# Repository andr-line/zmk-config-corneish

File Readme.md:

# Matrix keyboard
This is my attempt at making a keyboard that is as compact as possible but still useable, meaning that all the letter keys are still where they should be (just ortholinear). The pcb design is in hardware as a kicad file or as the finished gerber files I needed for pcbway.

## Important
This is my first keyboard, it‘s not perfect. The pcb does not include an off switch or reset button since I didn‘t find them important, as I will be using the keyboard quasy always and it did not really degrade the battery life too much for me. If you try to build this keyboard, **add a reset button** since pairing is extremely difficult without one.

The files are adapted to me, the bottom keys for example are shifted by one since I always typed like that. Also one of my controllers was faulty so I had to add an additional pin that is not needed normaly (pin 101).

## Unimportant
Recently I found the [36 key keyboard by dilshod](https://github.com/dilshod/36-choc-key-ortholinear-split) which is basically the same keyboard but with better execution. I am also planning on making a new version / revision that uses the kailh PG1316S switches (that are not yet commonly available as far as I know) as seen in [mikeholschers mikefive](https://github.com/mikeholscher/zmk-config-mikefive) keyboard as they could potentially reduce the thickness greatly.

[Keymap editor by nickcoutsos](https://nickcoutsos.github.io/keymap-editor/)

## Building instructions
You will need 36 choc v1 (Kailh 1350) switches, two nice!nano controllers, two batteries as recommended on the [nice!keyboards](https://nicekeyboards.com) site (I used the 301230 battery found on aliexpress as it fits nicely underneath the nice!nanos) and the machine pins to mount the nice!nano controllers to the board.

On the side where the silk screen (labels of the controllers pins) on the board are on top (will be covered by the battery) you have to solder the solder bridges as indicated by their frames. On the other board (where the silk screen is on the bottom) you have to solder them in the other way (solder the middle pad to the one that is not in the same frame). Then you have to solder the nice!nanos and batteries, and finally solder all the switches. Make sure that all solder connections are good.

If you haven't flashed the firmware yet, do it now and test if it works. You can connect each half via usb cable to test the hardware. If for some reason one of the pins of the nice!nano should breake (as was the case for me) you can use the 101, 102 and 107 pins in the middle of the nice!nano as backup (and change the files accordingly). To connect the two halves together you must reset them at the same time. This is very difficult without a reset button **hence you should add one** before ordering the pcbs. I managed to do it by bridging the reset pin using a pair of metal scissors on both halves simultaneously. Once this has worked you should be good to go. I recommend the above keymap editor to configure the keymap as it greatly simplifies the process.

## Final product
The keyboard looks like this, with an iPhone 11 for size comparison.

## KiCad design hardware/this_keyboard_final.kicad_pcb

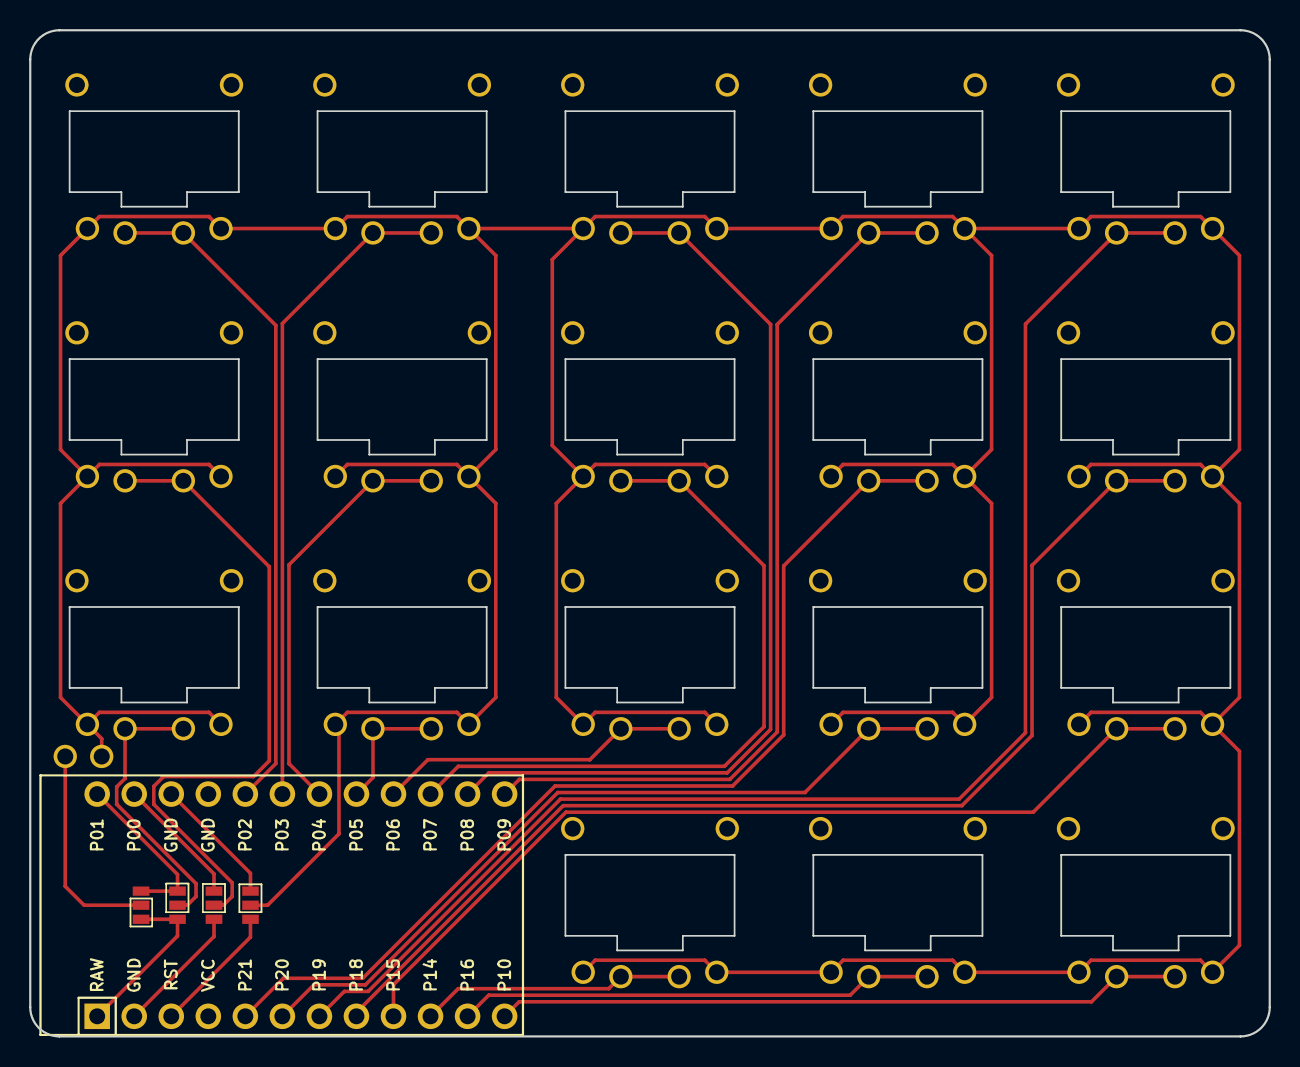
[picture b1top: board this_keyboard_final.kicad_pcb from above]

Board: 2 copper layers, 85.0 x 69.0 mm, 25 parts (0 on the bottom side), 24 nets.

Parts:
J1, J2: Kailh_PG1232
J3, J4, J5, J6: Jumper
MCU1: ProMicro
S1, S2, S3, S4, S5, S6, S7, S8, S9, S10, S11, S12, S13, S14, S15, S16, S17, S18: Kailh_PG1232

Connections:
GND: J1.1, J5.3, J6.1, MCU1.2, MCU1.15, MCU1.16, S1.1, S2.1, S3.1, S4.1, S5.1, S6.1, S7.1, S8.1, S9.1, S10.1, S11.1, S12.1, S13.1, S14.1, S15.1, S16.1, S17.1, S18.1
P0: J5.1, MCU1.14
P0_1: J5.1, S2.2
P1: J3.3, J4.1, MCU1.13
P1_1: J4.1, S1.2
P2: MCU1.17, S3.2
P3: MCU1.18, S6.2
P4: MCU1.19, S5.2
P5: MCU1.20, S4.2
P6: MCU1.21, S7.2
P7: MCU1.22, S8.2
P8: MCU1.23, S9.2
P9: MCU1.24, S12.2
P10: MCU1.12, S18.2
P14: MCU1.10, S16.2
P15: MCU1.9, S13.2
P16: MCU1.11, S17.2
P18: MCU1.8, S14.2
P19: MCU1.7, S15.2
P20: MCU1.6, S10.2
P21: MCU1.5, S11.2
RAW: J3.1, J4.3, MCU1.1
RAW_1: J2.1, J3.1
RST: J6.3, MCU1.3

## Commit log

2023-03-27 Initial User Config.
2023-03-27 Initial setup using zmk documentation
2023-03-27 changed things
2023-03-27 trying to get it to work
2023-03-27 Defined matrix cols manually
2023-03-27 added zmk/matrix.h
2023-03-27 Separated the two default transforms
2023-03-27 Using chosen ...=&matrix_left;
2023-03-27 Back to two different default_transforms
2023-03-28 Moved matrix_side definitions to matrix.dsi file
2023-03-28 Setup like vallacks piano
2023-03-28 Changed piano to matrix
2023-03-28 Changed offset to correct value
2023-03-28 Changed layer 0 and 1
2023-03-28 Fixed missing number after BT_SEL
2023-03-28 Fixed BSPC
2023-03-28 Added reset in top outside corners on layer 2
2023-03-28 Commented out 2nd and 3rd layer for testing
2023-03-28 Try try again
2023-03-28 Remade layer 0 and added reset
2023-03-28 Formatted and added bootloader and navigation
2023-03-28 Fixed backspace
2023-03-28 Added a reset combo for each half
2023-03-28 Added settings reset
2023-04-01 Added tab on left pinkie
2023-04-01 Changed right key definition
2023-04-03 Added layer definitions
2023-04-03 changed pin definition order
2023-04-03 Changed left key positions to match pin definition
2023-04-04 Added Pin 11 for testing
2023-04-18 Added a nice_nano pin definition for trial
2023-04-18 Removed pin 11
2023-04-19 Removed pin 11 because it wasnt working
2023-04-19 added hardware files
2023-04-19 Gitignore test
2023-04-19 Added readme
2023-04-19 Added image of keyboard
2023-04-19 Added image to readme
2023-04-20 Added gpio1 pin definition
2023-04-20 removed reset bindings
2023-04-20 Removed further reset binding
2023-08-15 Make both halves master for testing in Kconfig.defconfig
2023-08-15 Repaired right key layout
2023-08-15 Fixed spelling error
2023-08-15 Random key mask for trial and error
2023-08-15 more randomness
2023-08-15 randomness and commented layers
2023-08-15 randomnessi
2023-08-15 more random than bevore
2023-08-15 less random?
2023-08-15 less random
2023-08-15 DumeDruecke
2023-08-15 last pin
2023-08-15 it works
2023-08-15 Fixed board definition
2023-08-16 Made right halve slave
2024-03-26 Safety commit
2024-07-03 Moved keymap file
2024-07-04 Update layer 1
2024-07-04 Added building instructions
